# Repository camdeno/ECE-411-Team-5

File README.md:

# ECE-411-Team-5
This is our practicum project repository for ECE 411 Fall Term

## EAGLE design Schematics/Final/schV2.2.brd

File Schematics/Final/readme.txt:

This folder will contain the final schematic and board layout for the Door Lock project

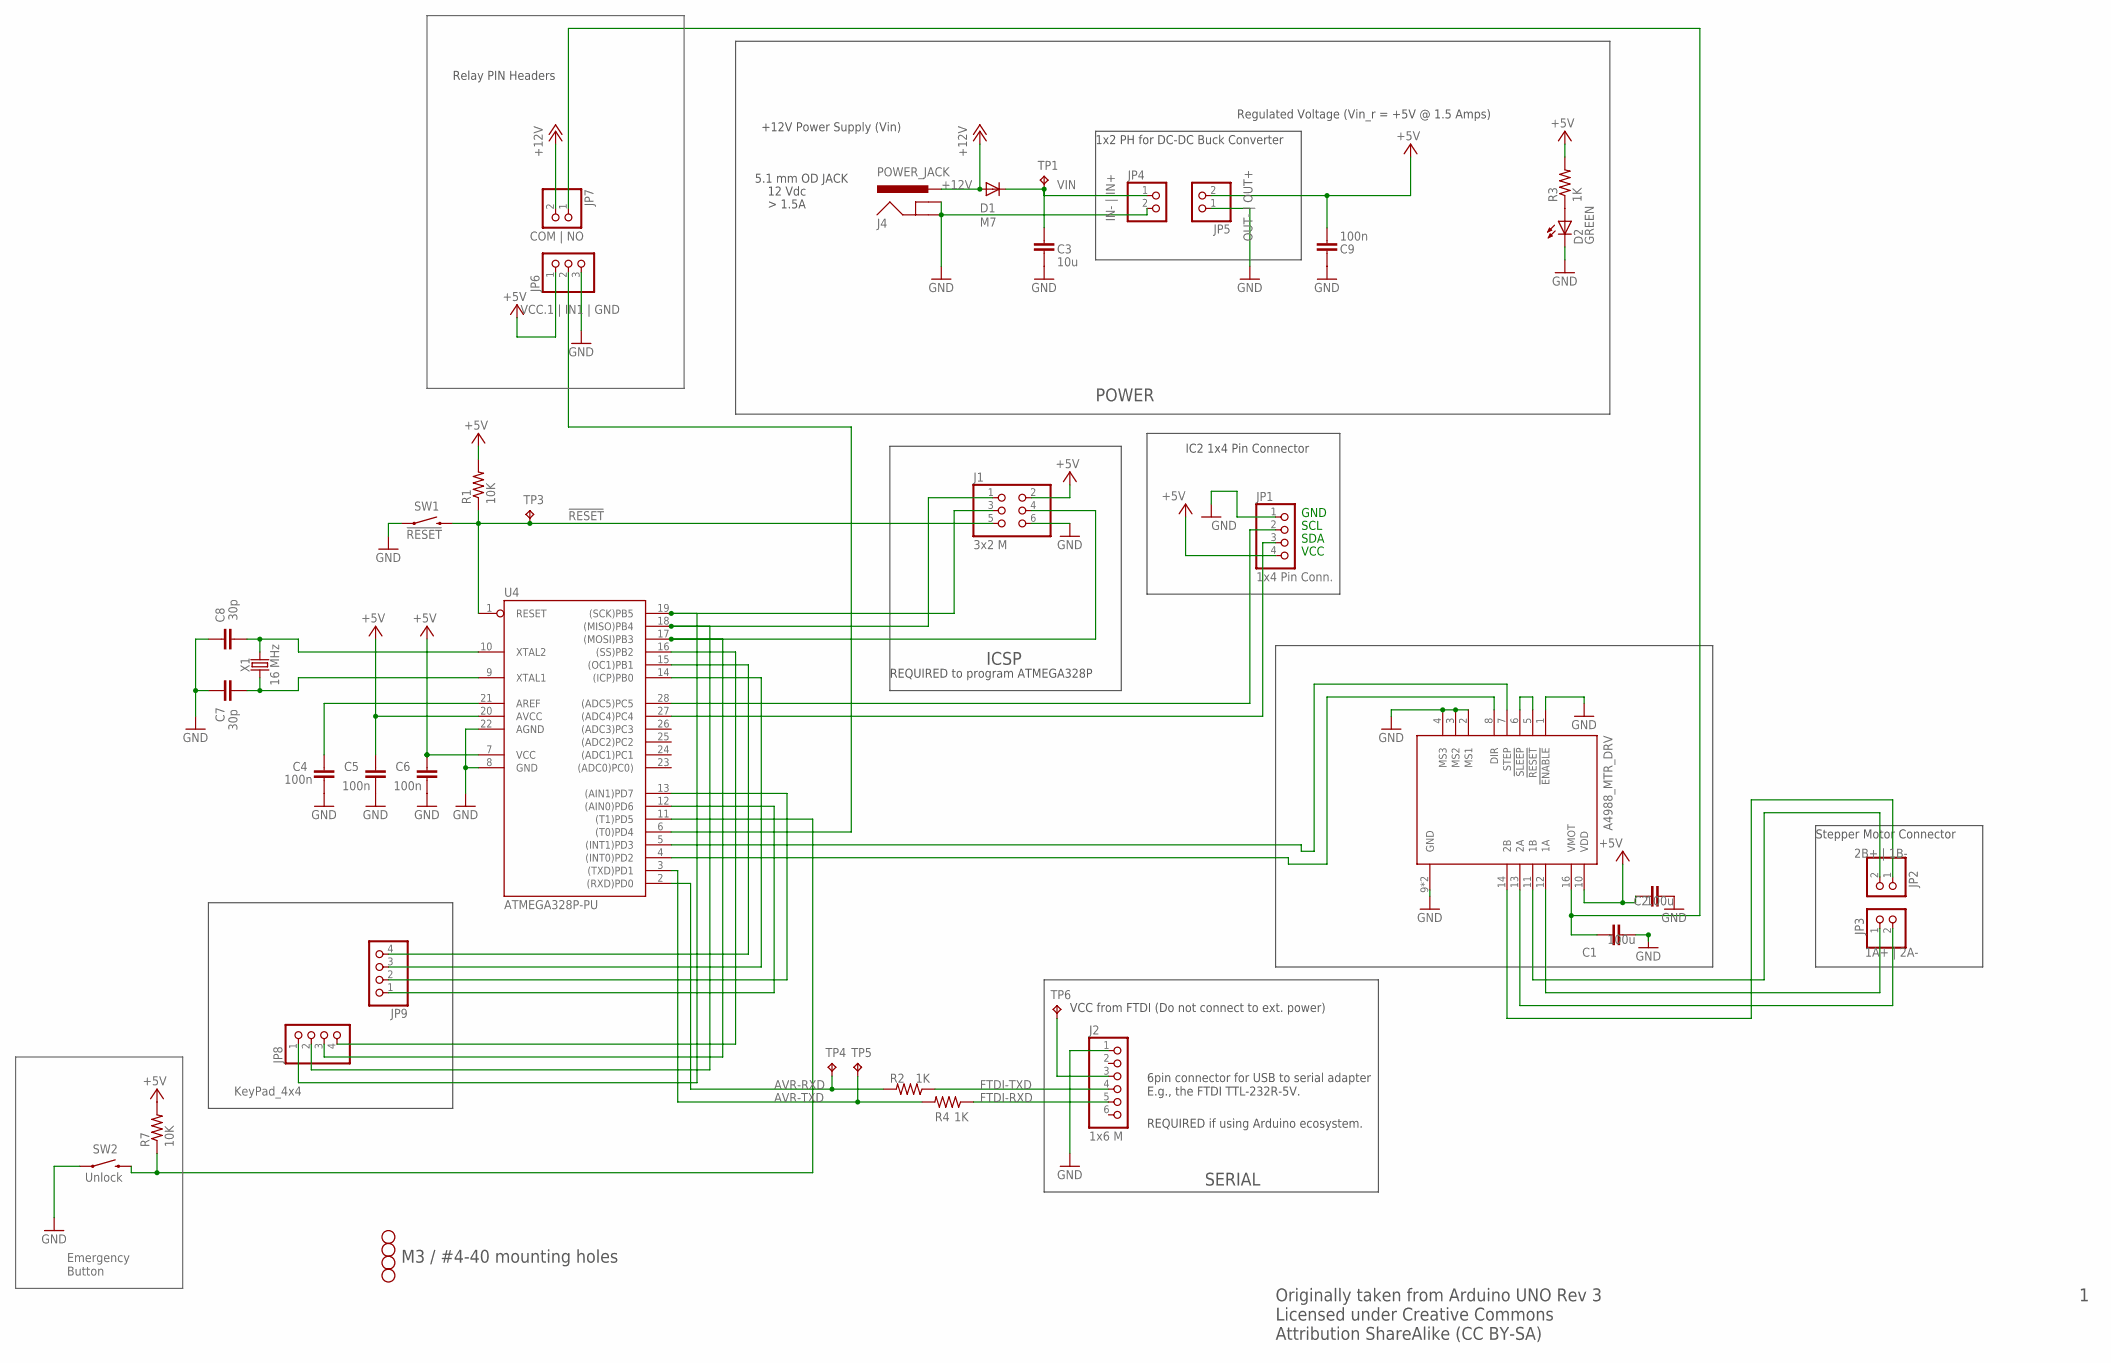
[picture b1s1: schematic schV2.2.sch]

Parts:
A4988_MTR_DRV: A4988_STEPPER_MOTOR_DRIVER_CARRIER; MODULE_A4988_STEPPER_MOTOR_DRIVER_CARRIER
C1, C2: 100u; C0805K; MPN CL21B104KBCNNNC
C3: 10u; C0805K; MPN CL21A106KOQNNNG
C4, C5, C6, C9: 100n; C0805K; MPN CL21B104KBCNNNC
C7: 30p; C0805K; MPN CL21C180JBANNNC
C8: 30p; C0805K; MPN CL21C300JBANNNC
D1: M7; SMB; MPN 10BQ030TR
D2: GREEN; CHIP-LED0805; MPN 150080GS75000
H1, H2, H3, H4: STAND-OFF
J1: 3x2 M; 2X03; MPN M20-9980345
J2: 1x6 M; 1X06; MPN PRPC006SAAN-RC
J4: POWER_JACK; POWER_JACK_PTH; MPN PJ-202A
JP1: 1x4 Pin Conn.; 1X04
JP2: 2B+ | 1B-; 1X02
JP3: 1A+ | 2A-; 1X02
JP4: IN- | IN+; 1X02
JP5: OUT- | OUT+; 1X02
JP6: VCC.1 | IN1 | GND; 1X03
JP7: COM | NO; 1X02
JP8, JP9: PINHD-1X4; 1X04
R1, R7: 10K; R0805; MPN RC0805FR-0710KL
R2, R3, R4: 1K; R0805; MPN RC0805FR-071KL
SW1: !RESET; TACTILE_SWITCH_SMD; MPN RS-187R05A2-DS MT RT
SW2: Unlock; TACTILE_SWITCH_SMD; MPN RS-187R05A2-DS MT RT
TP1, TP3, TP4, TP5, TP6: TPPAD1-13; P1-13
U4: ATMEGA328P-PU; DIL28-3; MPN ATMEGA328P-PU
X1: 16 MHz; HC49UP; MPN ECS-160-18-5PX-TR

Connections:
!RESET: J1.5, R1.1, SW1.3 (2), TP3.TP, U4.1 (RESET)
+5V: A4988_MTR_DRV.10 (VDD), C2.2, C5.2, C6.2, C9.2, J1.2, JP1.4, JP5.2, JP6.1, R1.2, R3.2, R7.2, U4.7 (VCC), U4.20 (AVCC)
+12V: D1.A, J4.PWR, JP7.2
AVR-RXD: R2.2, TP4.TP, U4.2 ((RXD)PD0)
AVR-TXD: R4.2, TP5.TP, U4.3 ((TXD)PD1)
FTDI-RXD: J2.5, R4.1
FTDI-TXD: J2.4, R2.1
GND: A4988_MTR_DRV.1 (!ENABLE), A4988_MTR_DRV.2 (MS1), A4988_MTR_DRV.3 (MS2), A4988_MTR_DRV.4 (MS3), A4988_MTR_DRV.9 (GND), A4988_MTR_DRV.15 (GND), C1.1, C2.1, C3.2, C4.1, C5.1, C6.1, C7.2, C8.2, C9.1, D2.C, J1.6, J2.1, J4.GND, J4.GNDBREAK, JP1.1, JP4.2, JP5.1, JP6.3, SW1.1, SW2.1, U4.8 (GND), U4.22 (AGND)
MISO: J1.1, JP8.2, U4.18 ((MISO)PB4)
MOSI: J1.4, JP8.3, U4.17 ((MOSI)PB3)
unnamed: C4.2, U4.21 (AREF)
unnamed: A4988_MTR_DRV.8 (DIR), U4.4 ((INT0)PD2)
unnamed: D2.A, R3.1
unnamed: A4988_MTR_DRV.7 (STEP), U4.5 ((INT1)PD3)
unnamed: J2.3, TP6.TP
unnamed: JP1.3, U4.27 ((ADC4)PC4)
unnamed: A4988_MTR_DRV.11 (1B), JP2.2
unnamed: A4988_MTR_DRV.12 (1A), JP3.1
unnamed: A4988_MTR_DRV.13 (2A), JP3.2
unnamed: A4988_MTR_DRV.14 (2B), JP2.1
unnamed: JP1.2, U4.28 ((ADC5)PC5)
unnamed: JP9.1, U4.12 ((AIN0)PD6)
unnamed: JP9.2, U4.13 ((AIN1)PD7)
unnamed: JP9.3, U4.14 ((ICP)PB0)
unnamed: JP9.4, U4.15 ((OC1)PB1)
unnamed: JP8.4, U4.16 ((SS)PB2)
unnamed: JP6.2, U4.6 ((T0)PD4)
unnamed: R7.1, SW2.3 (2), U4.11 ((T1)PD5)
unnamed: A4988_MTR_DRV.5 (!RESET), A4988_MTR_DRV.6 (!SLEEP)
unnamed: A4988_MTR_DRV.16 (VMOT), C1.2, JP7.1
SCK: J1.3, JP8.1, U4.19 ((SCK)PB5)
VIN: C3.1, D1.C, JP4.1, TP1.TP
XTAL1: C7.1, U4.9 (XTAL1), X1.1
XTAL2: C8.1, U4.10 (XTAL2), X1.2

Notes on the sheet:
POWER
ICSP
6pin connector for USB to serial adapter E.g., the FTDI TTL-232R-5V.
REQUIRED if using Arduino ecosystem.
M3 / #4-40 mounting holes
SERIAL
REQUIRED to program ATMEGA328P
VCC from FTDI (Do not connect to ext. power)
Originally taken from Arduino UNO Rev 3 Licensed under Creative Commons Attribution ShareAlike (CC BY-SA)
+12V Power Supply (Vin)
Regulated Voltage (Vin_r = +5V @ 1.5 Amps)
KeyPad_4x4
Emergency Button
GND
SCL
SDA
VCC
Stepper Motor Connector
IC2 1x4 Pin Connector
12 Vdc
5.1 mm OD JACK
1x2 PH for DC-DC Buck Converter
Relay PIN Headers

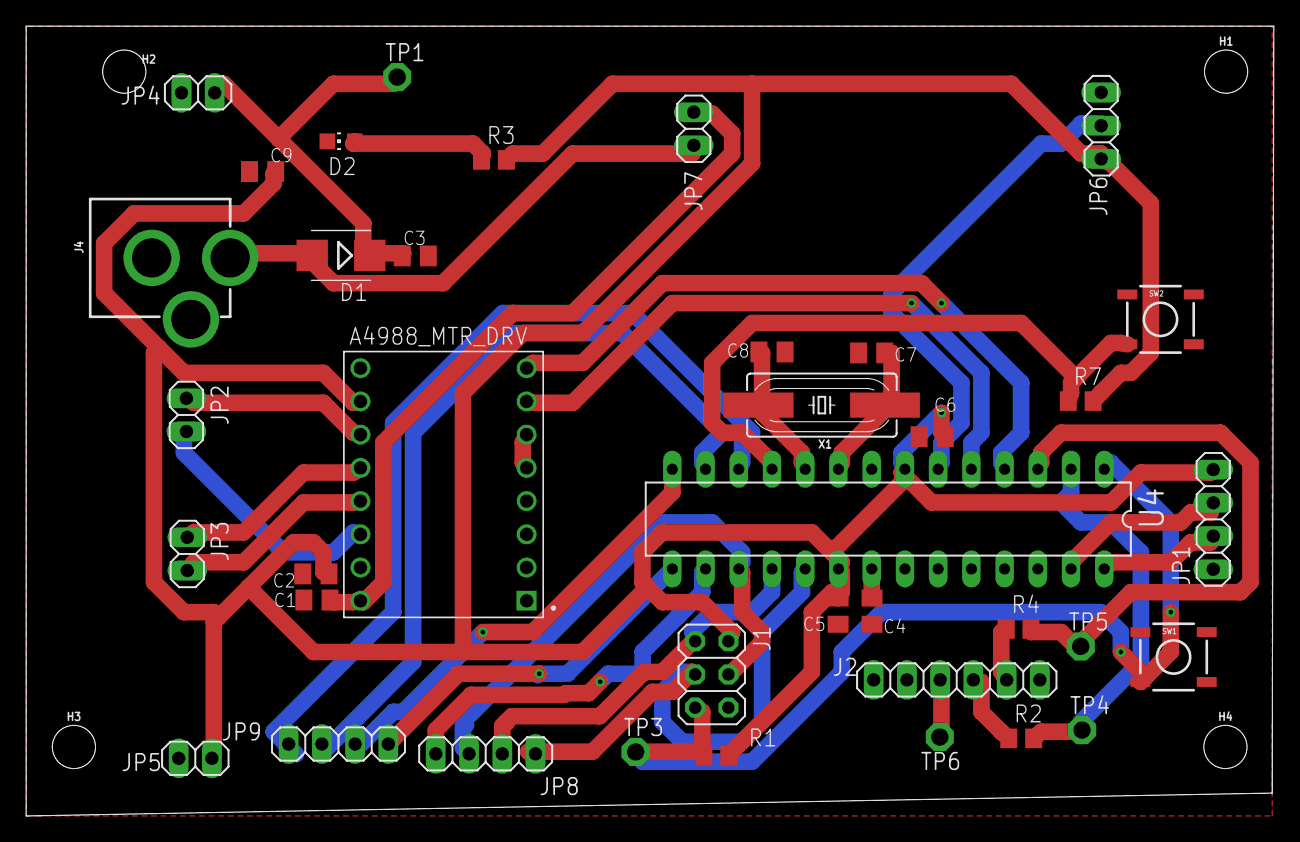
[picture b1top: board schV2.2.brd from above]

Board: 2 copper layers, 95.4 x 60.4 mm, 42 parts (0 on the bottom side), 34 nets.

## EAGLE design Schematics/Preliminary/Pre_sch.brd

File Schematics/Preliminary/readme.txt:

- Add the 'Preliminary' folder under C:\...\Documents\EAGLE\projects
- Open EAGLE and you should be able to see 'Preliminary' under projects->projects

OR

- Open EAGLE and create a new project
- Import the 'Pre_sch.sch' file into your project
- Click on 'Generate / Switch board' to create a board layout

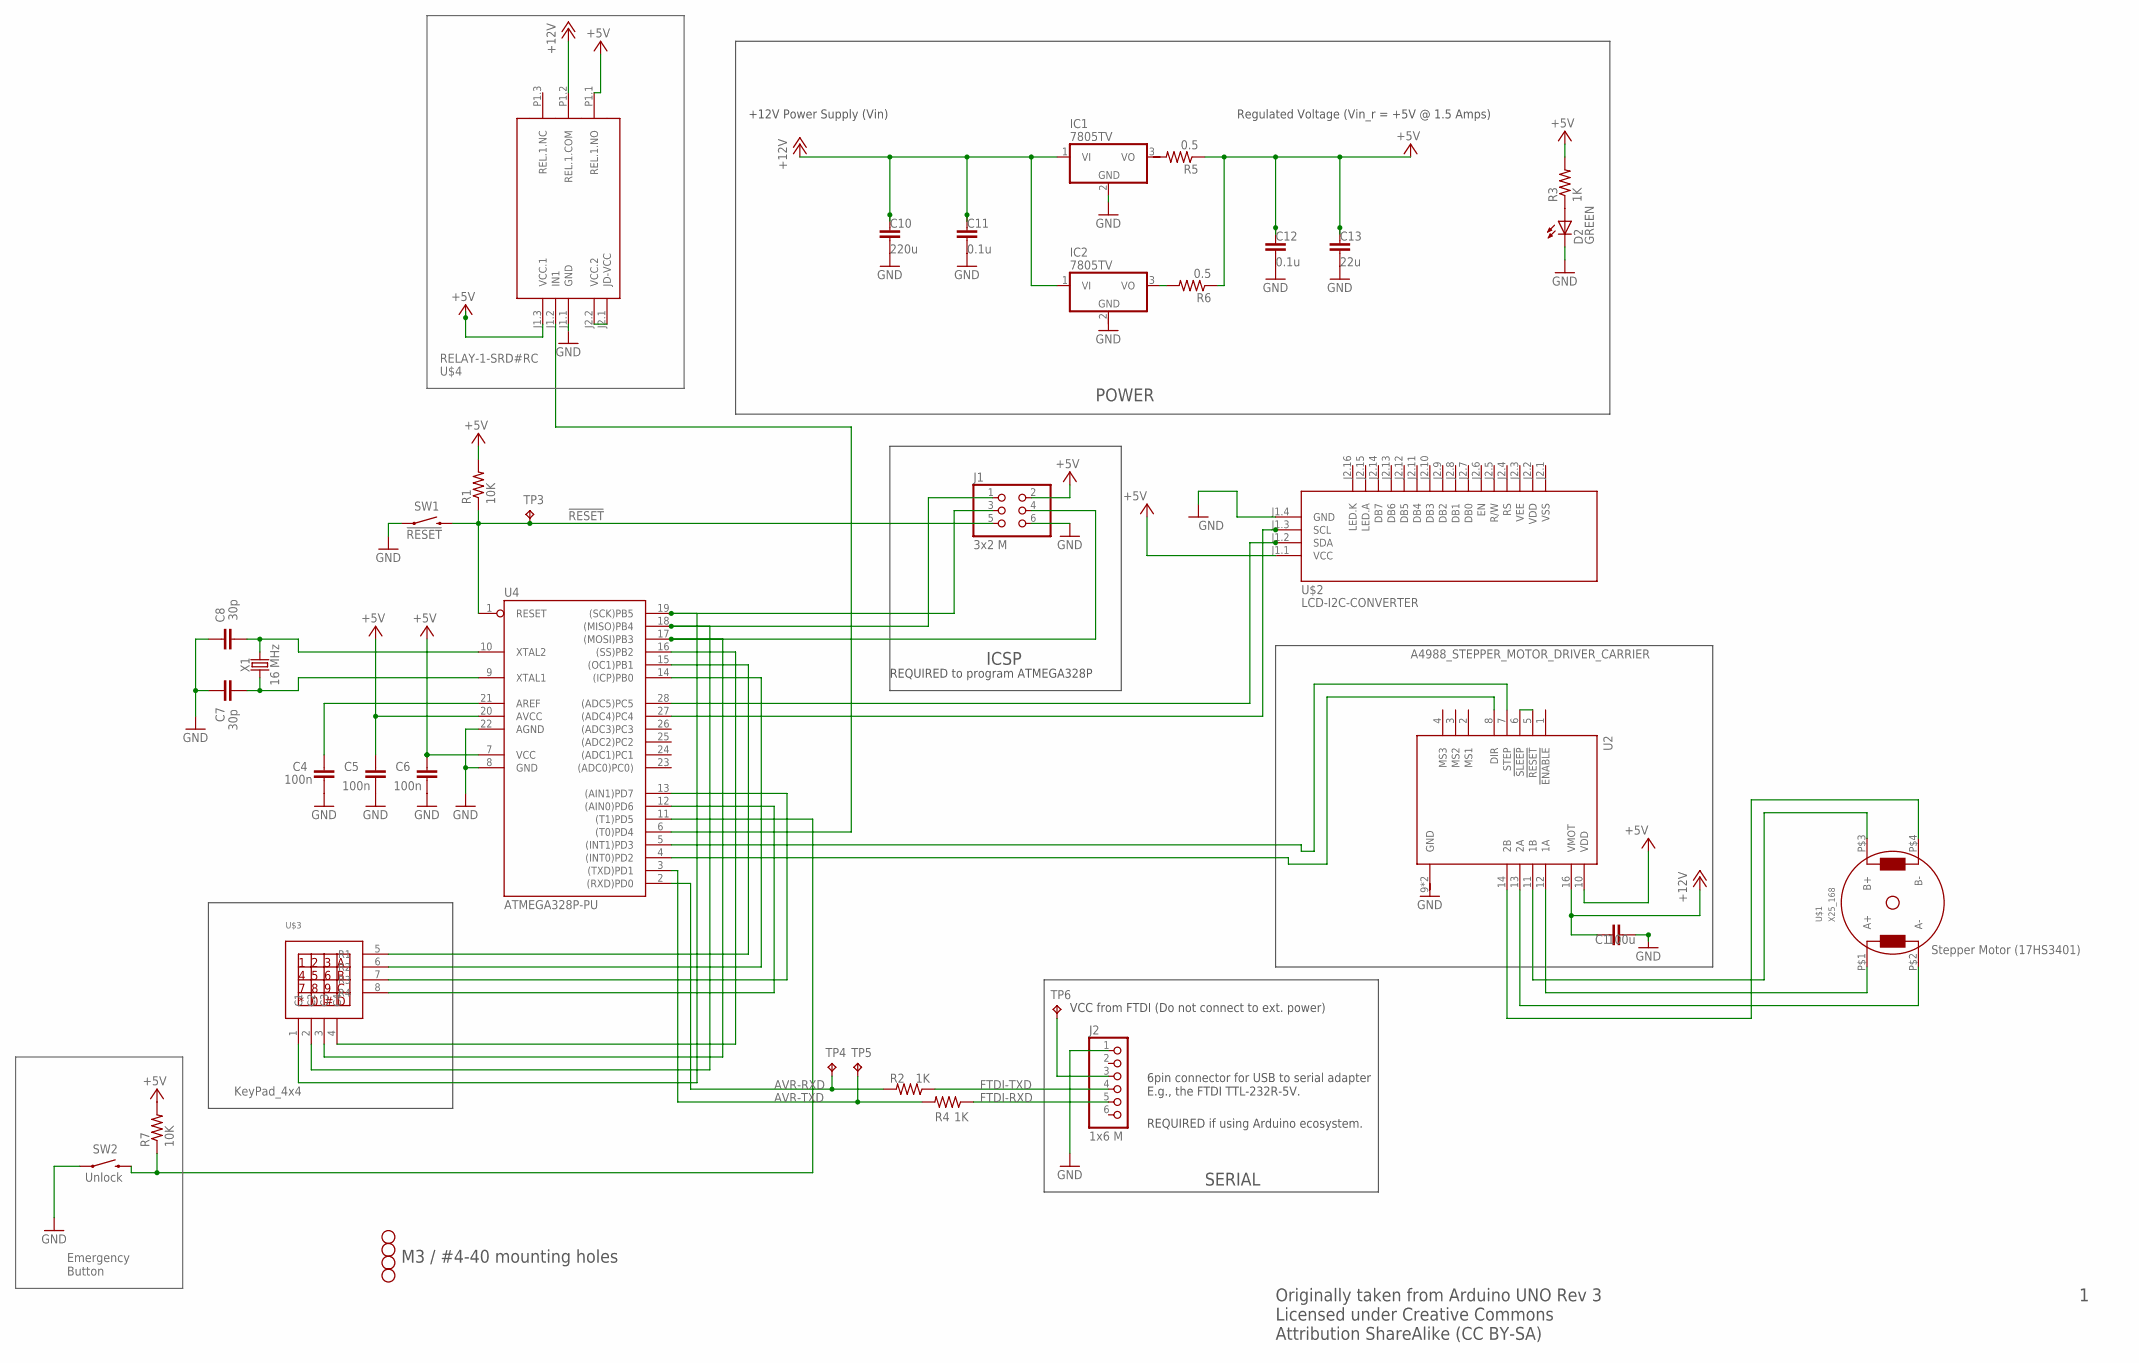
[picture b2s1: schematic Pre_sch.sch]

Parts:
C1: 100u; C0805K; MPN CL21B104KBCNNNC
C4, C5, C6: 100n; C0805K; MPN CL21B104KBCNNNC
C7: 30p; C0805K; MPN CL21C180JBANNNC
C8: 30p; C0805K; MPN CL21C300JBANNNC
C10: 220u; C0805K; MPN CL21B104KBCNNNC
C11, C12: 0.1u; C0805K; MPN CL21B104KBCNNNC
C13: 22u; C0805K; MPN CL21B104KBCNNNC
D2: GREEN; CHIP-LED0805; MPN 150080GS75000
H1, H2, H3, H4: STAND-OFF
IC1, IC2: 7805TV; TO220V
J1: 3x2 M; 2X03; MPN M20-9980345
J2: 1x6 M; 1X06; MPN PRPC006SAAN-RC
R1, R7: 10K; R0805; MPN RC0805FR-0710KL
R2, R3, R4: 1K; R0805; MPN RC0805FR-071KL
R5, R6: 0.5; R0805; MPN RC0805FR-071KL
SW1: !RESET; TACTILE_SWITCH_SMD; MPN RS-187R05A2-DS MT RT
SW2: Unlock; TACTILE_SWITCH_SMD; MPN RS-187R05A2-DS MT RT
TP3, TP4, TP5, TP6: TPPAD1-13; P1-13
U2: A4988_STEPPER_MOTOR_DRIVER_CARRIER; MODULE_A4988_STEPPER_MOTOR_DRIVER_CARRIER
U4: ATMEGA328P-PU; DIL28-3; MPN ATMEGA328P-PU
U$1: X25_168
U$2: LCD-I2C-CONVERTER
U$3: KEYPAD4X4
U$4: RELAY-1-SRD#RC
X1: 16 MHz; HC49UP; MPN ECS-160-18-5PX-TR

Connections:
!RESET: J1.5, R1.1, SW1.3 (2), TP3.TP, U4.1 (RESET)
+5V: C5.2, C6.2, C12.2, C13.2, J1.2, R1.2, R3.2, R5.1, R6.1, R7.2, U2.10 (VDD), U4.7 (VCC), U4.20 (AVCC), U$2.J1.1 (VCC), U$4.J1.3 (VCC.1), U$4.P1.1 (REL.1.NO)
+12V: C1.2, C10.2, C11.2, IC1.1 (VI), IC2.1 (VI), U2.16 (VMOT), U$4.P1.2 (REL.1.COM)
AVR-RXD: R2.2, TP4.TP, U4.2 ((RXD)PD0)
AVR-TXD: R4.2, TP5.TP, U4.3 ((TXD)PD1)
FTDI-RXD: J2.5, R4.1
FTDI-TXD: J2.4, R2.1
GND: C1.1, C4.1, C5.1, C6.1, C7.2, C8.2, C10.1, C11.1, C12.1, C13.1, D2.C, IC1.2 (GND), J1.6, J2.1, SW1.1, SW2.1, U2.9 (GND), U2.15 (GND), U4.8 (GND), U4.22 (AGND), U$2.J1.4 (GND), U$4.J1.1 (GND)
MISO: J1.1, U4.18 ((MISO)PB4), U$3.2 (C2)
MOSI: J1.4, U4.17 ((MOSI)PB3), U$3.3 (C3)
unnamed: C4.2, U4.21 (AREF)
unnamed: U2.8 (DIR), U4.4 ((INT0)PD2)
unnamed: D2.A, R3.1
unnamed: U2.7 (STEP), U4.5 ((INT1)PD3)
unnamed: J2.3, TP6.TP
unnamed: U4.27 ((ADC4)PC4), U$2.J1.3 (SCL)
unnamed: U2.5 (!RESET), U2.6 (!SLEEP)
unnamed: U2.11 (1B), U$1.P$3 (B+)
unnamed: U2.12 (1A), U$1.P$1 (A+)
unnamed: U2.13 (2A), U$1.P$2 (A-)
unnamed: U2.14 (2B), U$1.P$4 (B-)
unnamed: U4.28 ((ADC5)PC5), U$2.J1.2 (SDA)
unnamed: IC2.3 (VO), R6.2
unnamed: U4.12 ((AIN0)PD6), U$3.8 (R4)
unnamed: U4.13 ((AIN1)PD7), U$3.7 (R3)
unnamed: U4.14 ((ICP)PB0), U$3.6 (R2)
unnamed: U4.15 ((OC1)PB1), U$3.5 (R1)
unnamed: U4.16 ((SS)PB2), U$3.4 (C4)
unnamed: U$4.J2.1 (JD-VCC), U$4.J2.2 (VCC.2)
unnamed: U4.6 ((T0)PD4), U$4.J1.2 (IN1)
unnamed: R7.1, SW2.3 (2), U4.11 ((T1)PD5)
SCK: J1.3, U4.19 ((SCK)PB5), U$3.1 (C1)
XTAL1: C7.1, U4.9 (XTAL1), X1.1
XTAL2: C8.1, U4.10 (XTAL2), X1.2

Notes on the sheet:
POWER
ICSP
6pin connector for USB to serial adapter E.g., the FTDI TTL-232R-5V.
REQUIRED if using Arduino ecosystem.
M3 / #4-40 mounting holes
SERIAL
REQUIRED to program ATMEGA328P
VCC from FTDI (Do not connect to ext. power)
Originally taken from Arduino UNO Rev 3 Licensed under Creative Commons Attribution ShareAlike (CC BY-SA)
Stepper Motor (17HS3401)
+12V Power Supply (Vin)
Regulated Voltage (Vin_r = +5V @ 1.5 Amps)
KeyPad_4x4
Emergency Button

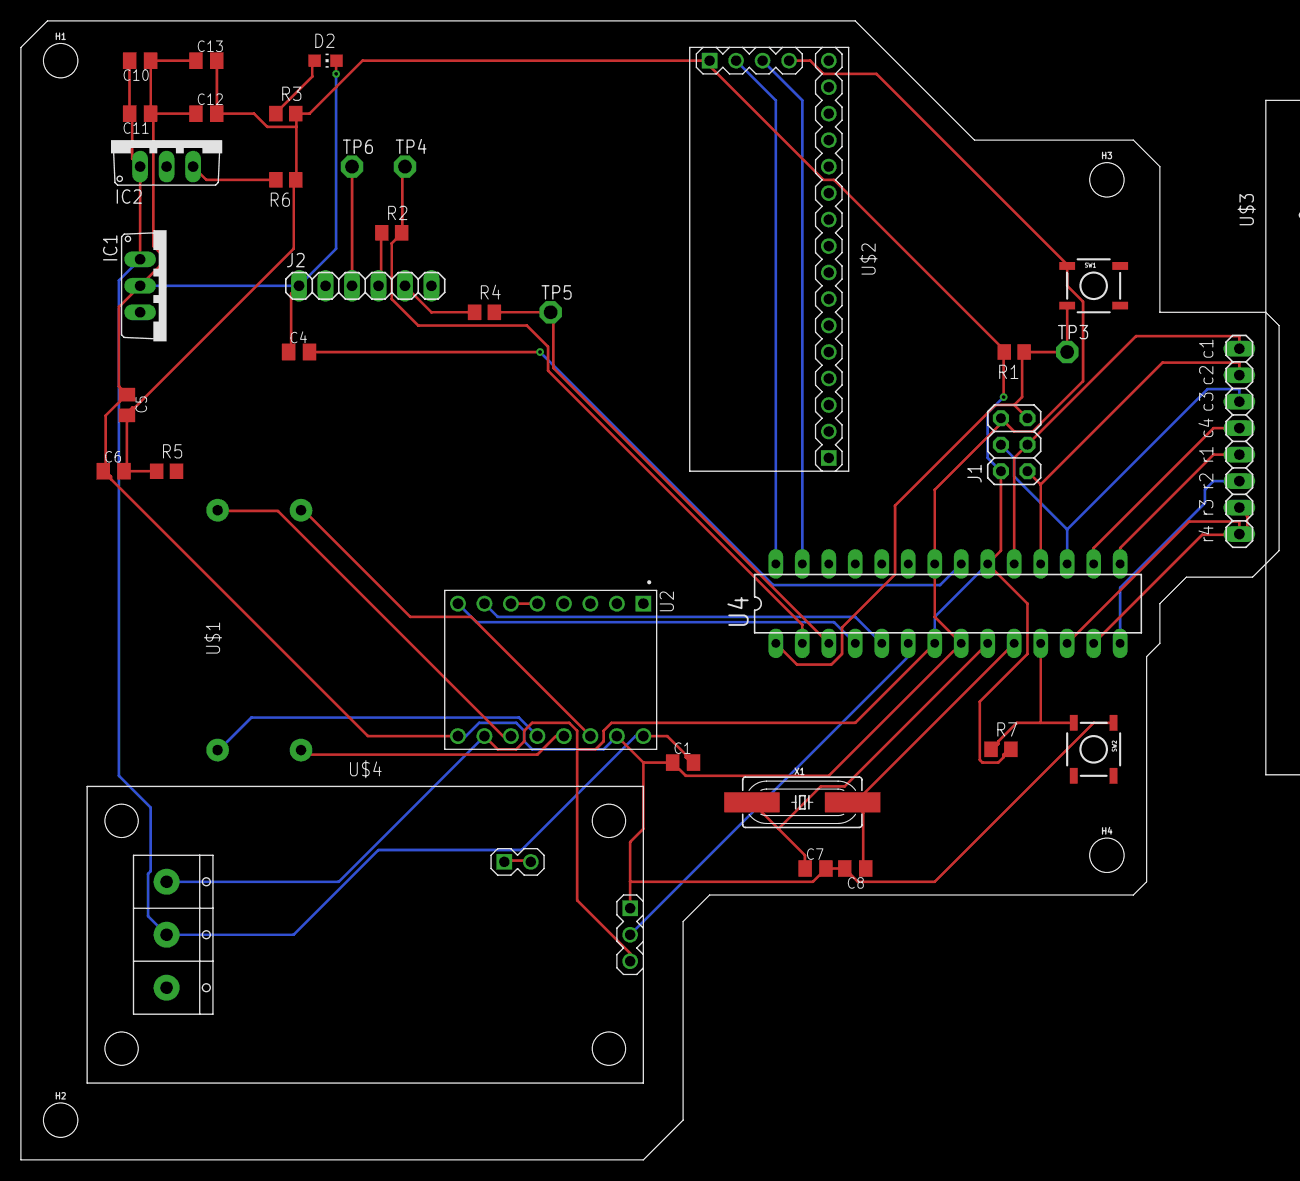
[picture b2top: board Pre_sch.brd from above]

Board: 2 copper layers, 120.7 x 109.2 mm, 39 parts (0 on the bottom side), 34 nets.

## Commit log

2020-11-02 Preliminary schematic initial commit
2020-11-02 Picture of Door Lock prototype
2020-11-02 Code in progress
2020-11-08 Created directory for schematics and board layout | Preliminary schematic is done | board layout needs organization
2020-11-08 Created folder 'Final' under 'Schematics'
2020-11-08 Better board template; still needs rearranging
2020-11-09 Preliminary Board Layout is done
2020-11-11 Initial BOM (.pdf & .xlsx)
2020-11-11 Minor Fix: a cell's boarder was missing
2020-11-12 Project Schedule
    This is our project schedule.
2020-11-16 Add files via upload
    The Stepper motor and IC2 was replaced with pin headers. The relay REL.1.NO is now connected to the stepper motor driver VMOT and bypass caps were added. The power supply still needs to be fixed.
2020-11-16 Add files via upload
    Pin headers were added for the stepper motor and IC2. The relay REL1.NO was connected to the stepper motor driver & by pass caps were added.
2020-11-16 Fixed ERC Errors and Warnings
2020-11-16 moved Pre_schV2.sch to Schematics/rough
2020-11-17 Add files via upload
    Relay & Buck converter pin headers were added
2020-11-17 Add files via upload
    Here is a smaller PCB design.
2020-11-18 Final Schematic and Board commited to Schematic/Final folder
2020-12-01 Completed Code -- still missing ability to change the keypad code
2020-12-02 Create Testing.md
    Created testing folder
2020-12-02 Uploaded Testing form for practicum HW
2020-12-06 Added hole for wires at the bottom of the face
2020-12-08 Minor Changes to wording
2020-12-08 Reviewed and Edited based on feedback
2020-12-08 added the date to the document
2020-12-08 Fixed the project schedule according to feedback
2020-12-08 Create the folder for the backup video
2020-12-08 back up video for presentation

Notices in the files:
parts and their libraries:
SparkFun-Hardware: Licensing: Creative Commons ShareAlike 4.0 International - https://creativecommons.org/licenses/by-sa/4.0
SparkFun-Electromechanical: Licensing: CC v3.0 Share-Alike You are welcome to use this library for commercial purposes.
